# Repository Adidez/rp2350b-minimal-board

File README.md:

# RP2350B Minimal Board — AI-Assisted, Gate-Verified KiCad Project

A Raspberry Pi **RP2350B (QFN-80)** minimal development board, taken from the official reference
design to a **fab-ready, evidence-verified state** by a gated, evidence-first hardware pipeline
with a human decision at every gate.

| | |
|---|---|
| MCU | RP2350B, QFN-80 10×10 mm (order **A4 stepping only** — E9 erratum fixed in A4) |
| Board | 52.6 × 72.1 mm, 2-layer, all 48 GPIOs broken out (8 ADC-capable) |
| Design state | Schematic **ERC: 0 errors** · PCB **DRC: 0 errors**, 73/73 nets connected |
| EDA | KiCad 10.0.4 (design migrated from the official KiCad 7 files, equivalence-proven) |

**Top view** — [checks/pcb_top.png](checks/pcb_top.png) · **Bottom** — [checks/pcb_bottom.png](checks/pcb_bottom.png) · **Schematic PDF** — [checks/schematic_review.pdf](checks/schematic_review.pdf)

## Open the design in KiCad

Two ways:
1. **No git needed**: download [RP2350B_minimal_kicad_project.zip](RP2350B_minimal_kicad_project.zip)
   (or the repo ZIP via *Code ▾ → Download ZIP*), unzip, then double-click
   `design/RP2350_80QFN_minimal.kicad_pro`.
2. `git clone https://github.com/Adidez/rp2350b-minimal-board && open design/RP2350_80QFN_minimal.kicad_pro`

Requires **KiCad 9 or 10** (files are v10 format; project-local symbol + footprint libraries and
the STEP model are included, so it opens fully self-contained — no library setup needed).

## What was actually done (the story)

1. **Stage 0 — Baseline.** Copied the official RP2350B minimal reference (KiCad 7) and migrated
   it under KiCad 10: installed global library tables (117 of 193 findings were phantom config
   noise), added the two missing `PWR_FLAG` declarations on the internal-VREG rails
   (`+1V1`, `VREG_AVDD`) that took ERC from 2 errors → 0, and re-linked a footprint KiCad 10
   renamed. Every schematic edit was proven by **netlist equivalence** — 75/75 nets,
   membership byte-identical.
2. **Stage 1 — Sourcing.** All 39 fitted parts got `MPN` + `LCSC` properties (hidden fields —
   the drawing stays clean) and a per-part datasheet corpus. Live-stock-checked ordering table:
   [checks/G1_gate_report.md](checks/G1_gate_report.md). One engineered substitution
   (Würth button → ALPS SKRPACE010, land-pattern-verified). 9 of 17 lines are JLCPCB Basic tier.
3. **Stage 2/3 — Layout verification.** The official routing was independently re-verified under
   modern checkers: 0 electrical DRC findings, full connectivity (511 segments / 48 vias /
   332 pads), USB pair geometry sound for full-speed, solid bottom GND plane. A false-positive
   severity policy from the KiCad-7 project file was fixed at root cause.
   Evidence: [checks/G3_prevalidation.md](checks/G3_prevalidation.md).
4. **Stage 4 — Fab package: DONE (Gate G4 PASS).** [fab/](fab/) holds the upload-ready set:
   [gerber zip](fab/RP2350B_minimal_gerbers.zip) (7 Protel-ext layers + PTH/NPTH drills,
   drill-count reconciled exactly against the design), [BOM](fab/bom_jlcpcb.csv) (17 lines,
   100% LCSC-resolved), [CPL](fab/cpl_jlcpcb.csv) (39 parts) and
   [ROTATION_NOTES.md](fab/ROTATION_NOTES.md). Release-gate evidence:
   [checks/G4_fab_release_gate.txt](checks/G4_fab_release_gate.txt).

Full audit trail: `git log` — every gate closes with its own commit and report in [checks/](checks/).

## Repository map

```
design/       The working KiCad project (schematic + routed PCB) — ERC/DRC clean
reference/    Official Raspberry Pi minimal design (untouched) + hardware design guide PDF
checks/       Gate reports + ERC/DRC JSON evidence + renders (the generated documents)
datasheets/   Per-MPN vendor datasheets (17) + manifest
fab/          JLCPCB-ready package: gerber zip, assembly BOM (LCSC), CPL, rotation notes
.claude/      The pipeline skill: stage gates, RP2350B design rules, toolchain quirks
```

## The design rules that matter (and that generic AI gets wrong)

- **A4 stepping only** (`RP2350B0A4`, LCSC C9900208890): A2 has erratum E9 (GPIO input-mode
  leakage ~120 µA, latches ~2.2 V). Verify at bring-up via `rp2350_chip_version()`.
- The RP2350 core regulator is a **switcher, not an LDO**: the 3.3 µH inductor
  (Abracon AOTA-B201610S3R3, **polarity dot**) is mandatory.
- `QSPI_SS` is the BOOTSEL strap and `QSPI SD1` selects the bootloader interface — neither may
  be loaded or biased at reset.
- Crystal is CL=10 pF (ABM8-272-T3) with tuned damping — don't substitute a 20 pF part without
  re-deriving load caps.
- Full list with sources: [.claude/skills/rp2350b-hardware-pipeline/references/rp2350b-design-rules.md](.claude/skills/rp2350b-hardware-pipeline/references/rp2350b-design-rules.md)

## Reproduce the verification yourself

```bash
KCLI=/Applications/KiCad/KiCad.app/Contents/MacOS/kicad-cli   # macOS bundle path
$KCLI sch erc --severity-all --output /tmp/erc.rpt design/RP2350_80QFN_minimal.kicad_sch   # → 0 errors
$KCLI pcb drc --severity-all --refill-zones --output /tmp/drc.rpt design/RP2350_80QFN_minimal.kicad_pcb  # → 0 errors
$KCLI pcb render --side top --output /tmp/top.png design/RP2350_80QFN_minimal.kicad_pcb
```

Expected residual warnings are documented (66 `endpoint_off_grid` + 6 `lib_symbol_mismatch` on
the schematic; 52 metadata findings on the PCB) — see the gate reports for the keep-rationale.

## Remaining path to a live board (human steps)

1. **Order at JLCPCB**: upload [fab/RP2350B_minimal_gerbers.zip](fab/RP2350B_minimal_gerbers.zip) +
   [BOM](fab/bom_jlcpcb.csv) + [CPL](fab/cpl_jlcpcb.csv). In the assembly preview, verify
   orientation of U1/U2/U3/J1/L1/Y1 against [checks/pcb_top.png](checks/pcb_top.png) — see
   [fab/ROTATION_NOTES.md](fab/ROTATION_NOTES.md). RP2350B **A4** (C9900208890) is a
   global-sourcing part — reserve early; re-verify all Extended-tier stock (table dated
   2026-07-07). Pick **Standard** assembly if J2/J3 headers should be machine-placed
   (Economic = SMD-only → hand-solder the headers).
2. **Bring-up**: 3V3 → 1V1 (proves VREG + inductor) → hold BOOTSEL, plug USB → mass-storage
   enumeration → flash a UF2 → confirm **A4** in silicon via `rp2350_chip_version()`.

## Attribution & licenses

- Base design: **Raspberry Pi Ltd** — "RP2350B QFN80 Minimal Design Example" from
  [Hardware design with RP2350](https://datasheets.raspberrypi.com/rp2350/hardware-design-with-rp2350.pdf)
  (© Raspberry Pi Ltd, redistributed with attribution; reference copy unmodified in `reference/`).
- Vendor datasheets in `datasheets/` remain the property of their respective manufacturers
  (Winbond, onsemi, Abracon, Samsung, UNI-ROYAL, ALPS, JST, Amphenol, XKB, Raspberry Pi).
- Verification tooling: [KiCad](https://kicad.org) 10.0.4 · [kicad-happy](https://github.com/aklofas/kicad-happy)
  (analysis) · [KiCadRoutingTools](https://github.com/drandyhaas/KiCadRoutingTools) (post-route checks).
- Pipeline definition: project-specific gated skill
  ([.claude/skills/rp2350b-hardware-pipeline](.claude/skills/rp2350b-hardware-pipeline)).

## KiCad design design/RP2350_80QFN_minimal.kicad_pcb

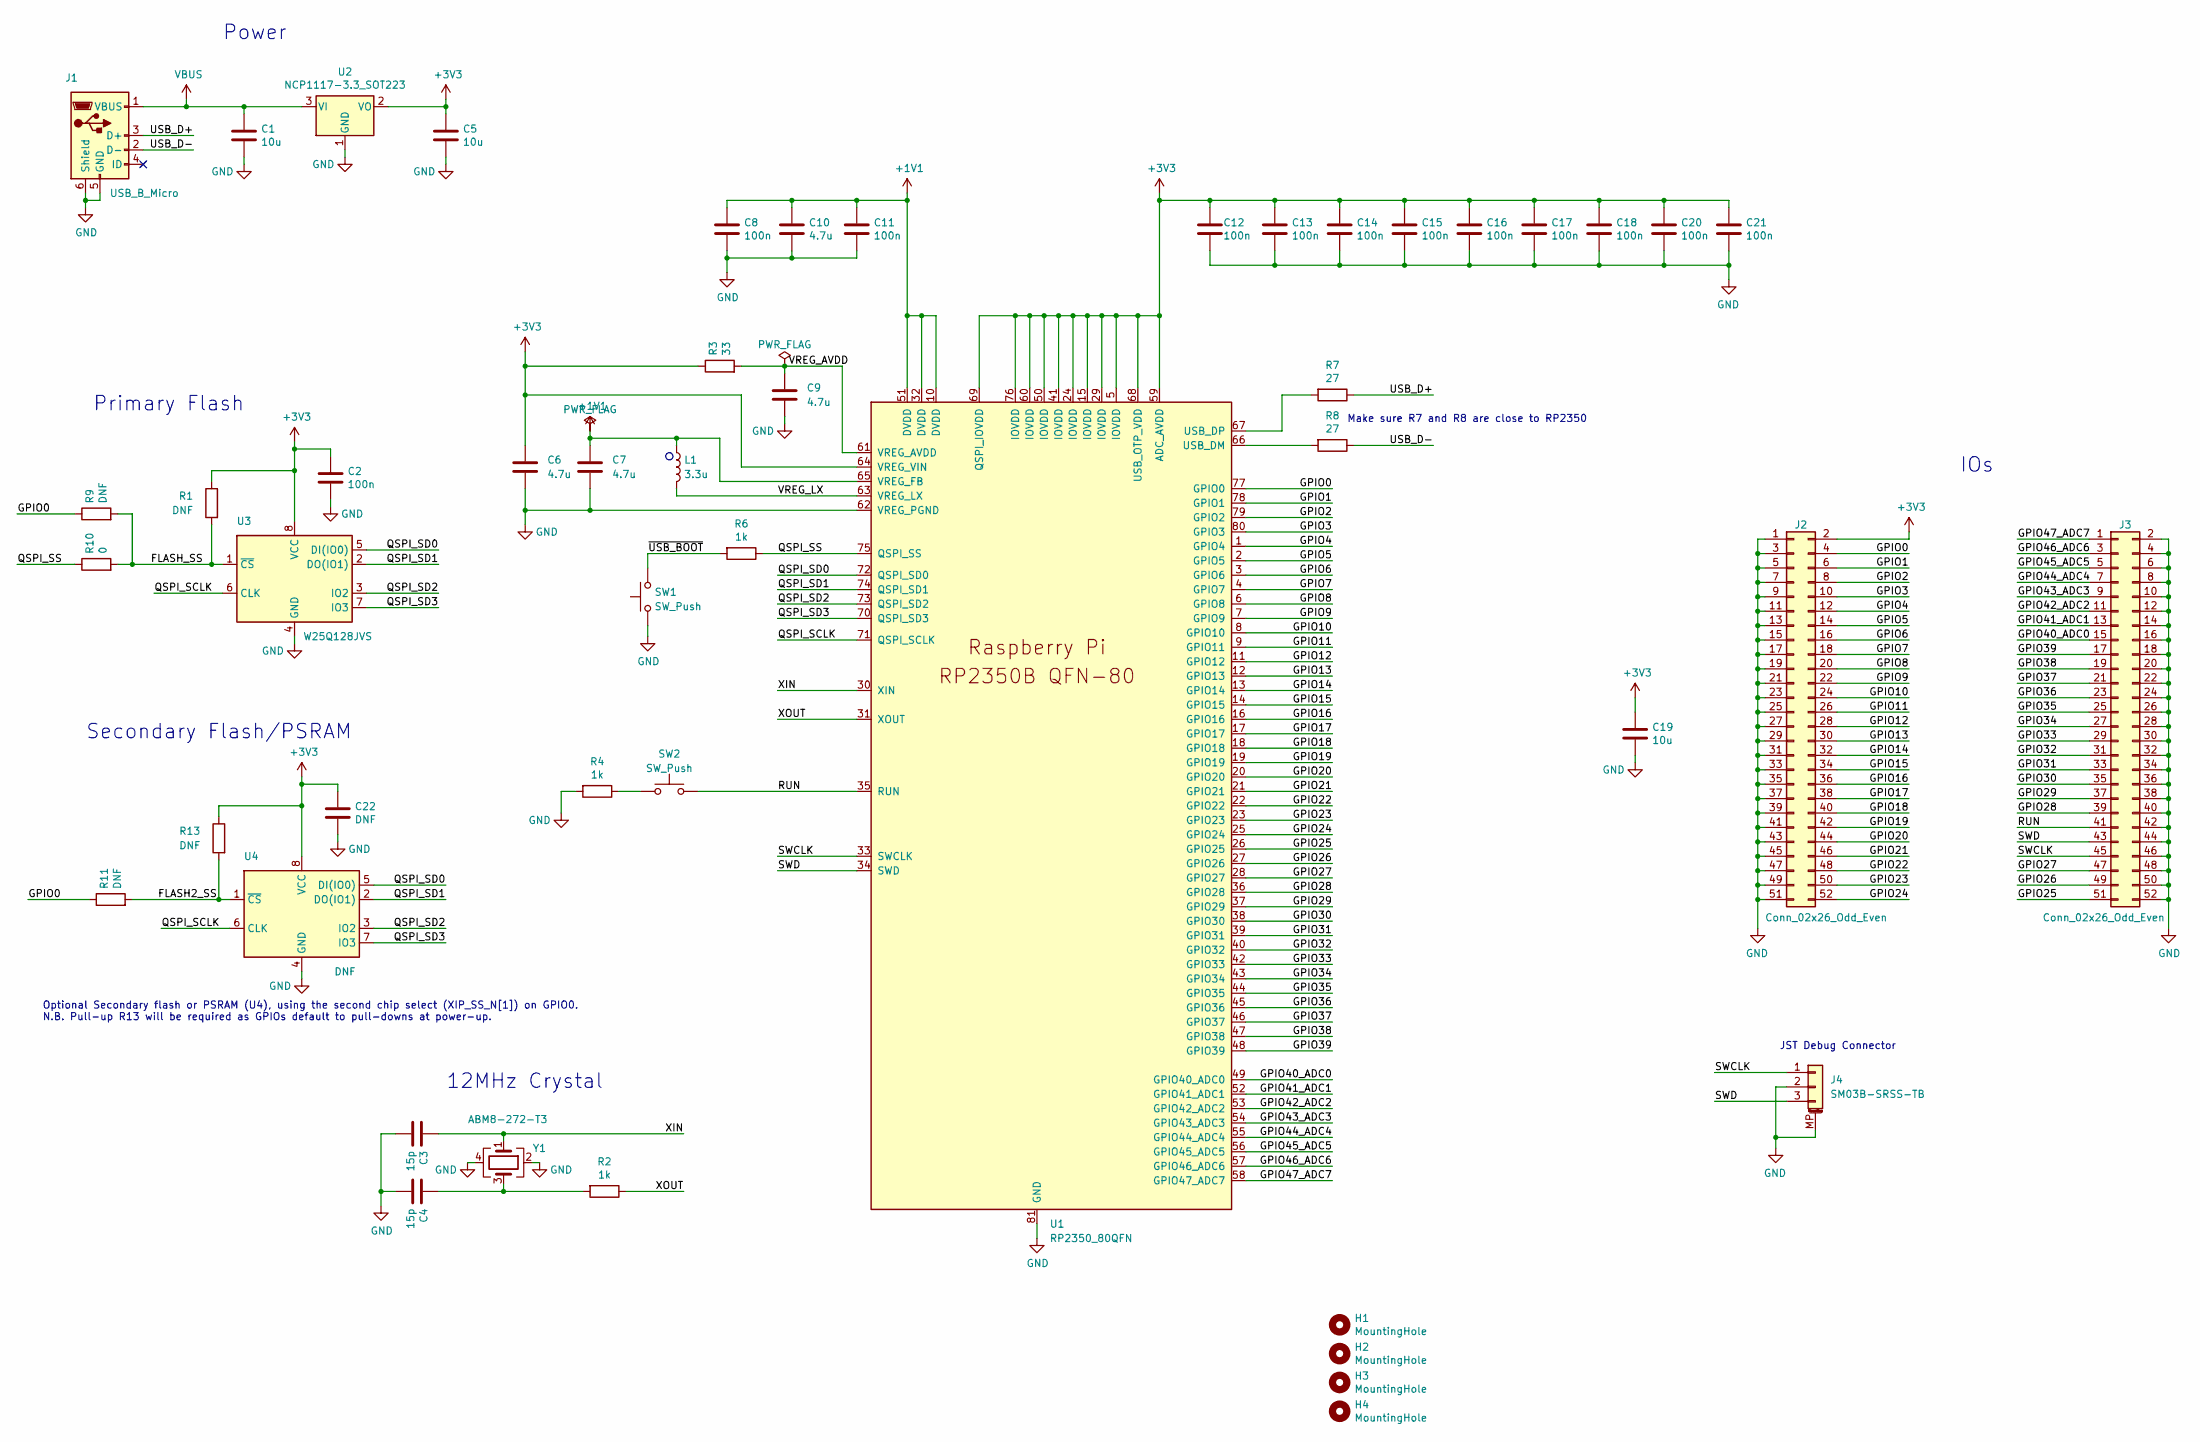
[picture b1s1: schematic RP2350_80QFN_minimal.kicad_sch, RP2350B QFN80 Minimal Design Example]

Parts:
C1, C5, C19: 10u; C_0805_2012Metric; MPN CL21A106KAYNNNE; LCSC C15850
C2, C8, C11, C12, C13, C14, C15, C16, C17, C18, C20, C21: 100n; C_0402_1005Metric; MPN CL05B104KO5NNNC; LCSC C1525
C3, C4: 15p; C_0402_1005Metric; MPN 0402CG150J500NT; LCSC C1548
C6, C7: 4.7u; C_0402_1005Metric_small_pads; MPN CL05A475MP5NRNC; LCSC C23733
C9, C10: 4.7u; C_0402_1005Metric; MPN CL05A475MP5NRNC; LCSC C23733
C22: DNF; C_0402_1005Metric
H1, H2, H3, H4: MountingHole; MountingHole_2.7mm_M2.5
J1: USB_B_Micro; USB_Micro-B_Amphenol_10103594-0001LF_Horizontal; MPN 10103594-0001LF; LCSC C428495
J2, J3: Conn_02x26_Odd_Even; PinHeader_2x26_P2.54mm_Vertical; MPN X6521WV-2x26H-C60D30; LCSC C725898
J4: SM03B-SRSS-TB; JST_SH_SM03B-SRSS-TB_1x03-1MP_P1.00mm_Horizontal; MPN SM03B-SRSS-TB(LF)(SN); LCSC C160403
L1: 3.3u; L_pol_2016; MPN AOTA-B201610S3R3-101-T; LCSC C42411119
R1, R9, R11, R13: DNF; R_0402_1005Metric
R2, R4, R6: 1k; R_0402_1005Metric; MPN 0402WGF1001TCE; LCSC C11702
R3: 33; R_0402_1005Metric; MPN 0402WGF330JTCE; LCSC C25105
R7, R8: 27; R_0402_1005Metric; MPN 0402WGF270JTCE; LCSC C25100
R10: 0; R_0402_1005Metric; MPN 0402WGF0000TCE; LCSC C17168
SW1, SW2: SW_Push; SW_Push_1P1T_NO_Vertical_Wuerth_434133025816; MPN SKRPACE010; LCSC C139797
U1: RP2350_80QFN; RP2350-QFN-80-1EP_10x10_P0.4mm_EP3.4x3.4mm_ThermalVias; MPN RP2350B A4; LCSC C9900208890
U2: NCP1117-3.3_SOT223; SOT-223-3_TabPin2; MPN NCP1117ST33T3G; LCSC C26537
U3: W25Q128JVS; SOIC-8_5.3x5.3mm_P1.27mm; MPN W25Q128JVSIQ; LCSC C97521
U4: DNF; SOIC-8_5.3x5.3mm_P1.27mm
Y1: ABM8-272-T3; Crystal_SMD_3225-4Pin_3.2x2.5mm; MPN ABM8-272-T3; LCSC C20625731

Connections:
+1V1: C7.1, C8.1, C10.1, C11.1, L1.1, U1.10 (DVDD), U1.32 (DVDD), U1.51 (DVDD), U1.65 (VREG_FB)
+3V3: C2.1, C5.1, C6.1, C12.1, C13.1, C14.1, C15.1, C16.1, C17.1, C18.1, C19.1, C20.1, C21.1, C22.1, J2.2, R1.1, R3.1, R13.1, U1.5 (IOVDD), U1.15 (IOVDD), U1.24 (IOVDD), U1.29 (IOVDD), U1.41 (IOVDD), U1.50 (IOVDD), U1.59 (ADC_AVDD), U1.60 (IOVDD), U1.64 (VREG_VIN), U1.68 (USB_OTP_VDD), U1.69 (QSPI_IOVDD), U1.76 (IOVDD), U2.2 (VO), U3.8 (VCC), U4.8 (VCC)
/FLASH2_SS: R11.2, R13.2, U4.1 (~CS)
/FLASH_SS: R1.2, R9.2, R10.2, U3.1 (~CS)
/GPIO0: J2.4, R9.1, R11.1, U1.77 (GPIO0)
/GPIO1: J2.6, U1.78 (GPIO1)
/GPIO2: J2.8, U1.79 (GPIO2)
/GPIO3: J2.10, U1.80 (GPIO3)
/GPIO4: J2.12, U1.1 (GPIO4)
/GPIO5: J2.14, U1.2 (GPIO5)
/GPIO6: J2.16, U1.3 (GPIO6)
/GPIO7: J2.18, U1.4 (GPIO7)
/GPIO8: J2.20, U1.6 (GPIO8)
/GPIO9: J2.22, U1.7 (GPIO9)
/GPIO10: J2.24, U1.8 (GPIO10)
/GPIO11: J2.26, U1.9 (GPIO11)
/GPIO12: J2.28, U1.11 (GPIO12)
/GPIO13: J2.30, U1.12 (GPIO13)
/GPIO14: J2.32, U1.13 (GPIO14)
/GPIO15: J2.34, U1.14 (GPIO15)
/GPIO16: J2.36, U1.16 (GPIO16)
/GPIO17: J2.38, U1.17 (GPIO17)
/GPIO18: J2.40, U1.18 (GPIO18)
/GPIO19: J2.42, U1.19 (GPIO19)
/GPIO20: J2.44, U1.20 (GPIO20)
/GPIO21: J2.46, U1.21 (GPIO21)
/GPIO22: J2.48, U1.22 (GPIO22)
/GPIO23: J2.50, U1.23 (GPIO23)
/GPIO24: J2.52, U1.25 (GPIO24)
/GPIO25: J3.51, U1.26 (GPIO25)
/GPIO26: J3.49, U1.27 (GPIO26)
/GPIO27: J3.47, U1.28 (GPIO27)
/GPIO28: J3.39, U1.36 (GPIO28)
/GPIO29: J3.37, U1.37 (GPIO29)
/GPIO30: J3.35, U1.38 (GPIO30)
/GPIO31: J3.33, U1.39 (GPIO31)
/GPIO32: J3.31, U1.40 (GPIO32)
/GPIO33: J3.29, U1.42 (GPIO33)
/GPIO34: J3.27, U1.43 (GPIO34)
/GPIO35: J3.25, U1.44 (GPIO35)
/GPIO36: J3.23, U1.45 (GPIO36)
/GPIO37: J3.21, U1.46 (GPIO37)
/GPIO38: J3.19, U1.47 (GPIO38)
/GPIO39: J3.17, U1.48 (GPIO39)
/GPIO40_ADC0: J3.15, U1.49 (GPIO40_ADC0)
/GPIO41_ADC1: J3.13, U1.52 (GPIO41_ADC1)
/GPIO42_ADC2: J3.11, U1.53 (GPIO42_ADC2)
/GPIO43_ADC3: J3.9, U1.54 (GPIO43_ADC3)
/GPIO44_ADC4: J3.7, U1.55 (GPIO44_ADC4)
/GPIO45_ADC5: J3.5, U1.56 (GPIO45_ADC5)
/GPIO46_ADC6: J3.3, U1.57 (GPIO46_ADC6)
/GPIO47_ADC7: J3.1, U1.58 (GPIO47_ADC7)
/QSPI_SCLK: U1.71 (QSPI_SCLK), U3.6 (CLK), U4.6 (CLK)
/QSPI_SD0: U1.72 (QSPI_SD0), U3.5 (DI(IO0)), U4.5 (DI(IO0))
/QSPI_SD1: U1.74 (QSPI_SD1), U3.2 (DO(IO1)), U4.2 (DO(IO1))
/QSPI_SD2: U1.73 (QSPI_SD2), U3.3 (IO2), U4.3 (IO2)
/QSPI_SD3: U1.70 (QSPI_SD3), U3.7 (IO3), U4.7 (IO3)
/QSPI_SS: R6.1, R10.1, U1.75 (QSPI_SS)
/RUN: J3.41, SW2.2, U1.35 (RUN)
/SWCLK: J3.45, J4.1, U1.33 (SWCLK)
/SWD: J3.43, J4.3, U1.34 (SWD)
/USB_D+: J1.3 (D+), R7.1
/USB_D-: J1.2 (D-), R8.1
/VREG_AVDD: C9.1, R3.2, U1.61 (VREG_AVDD)
/VREG_LX: L1.2, U1.63 (VREG_LX)
/XIN: C3.1, U1.30 (XIN), Y1.1
/XOUT: R2.1, U1.31 (XOUT)
/~USB_BOOT: R6.2, SW1.2
GND: C1.2, C2.2, C3.2, C4.2, C5.2, C6.2, C7.2, C8.2, C9.2, C10.2, C11.2, C12.2, C13.2, C14.2, C15.2, C16.2, C17.2, C18.2, C19.2, C20.2, C21.2, C22.2, J1.5 (GND), J1.6 (Shield), J2.1, J2.3, J2.5, J2.7, J2.9, J2.11, J2.13, J2.15, J2.17, J2.19, J2.21, J2.23, J2.25, J2.27, J2.29, J2.31, J2.33, J2.35, J2.37, J2.39, J2.41, J2.43, J2.45, J2.47, J2.49, J2.51, J3.2, J3.4, J3.6, J3.8, J3.10, J3.12, J3.14, J3.16, J3.18, J3.20, J3.22, J3.24, J3.26, J3.28, J3.30, J3.32, J3.34, J3.36, J3.38, J3.40, J3.42, J3.44, J3.46, J3.48, J3.50, J3.52, J4.2, J4.MP (MountPin), R4.2, SW1.1, U1.62 (VREG_PGND), U1.81 (GND), U2.1 (GND), U3.4 (GND), U4.4 (GND), Y1.2, Y1.4
unnamed: C4.1, R2.2, Y1.3
unnamed: R4.1, SW2.1
unnamed: R8.2, U1.66 (USB_DM)
unnamed: R7.2, U1.67 (USB_DP)
VBUS: C1.1, J1.1 (VBUS), U2.3 (VI)

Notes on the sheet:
Optional Secondary flash or PSRAM (U4), using the second chip select (XIP_SS_N[1]) on GPIO0. N.B. Pull-up R13 will be required as GPIOs default to pull-downs at power-up.
IOs
12MHz Crystal
Primary Flash
JST Debug Connector
Make sure R7 and R8 are close to RP2350
Secondary Flash/PSRAM
Power

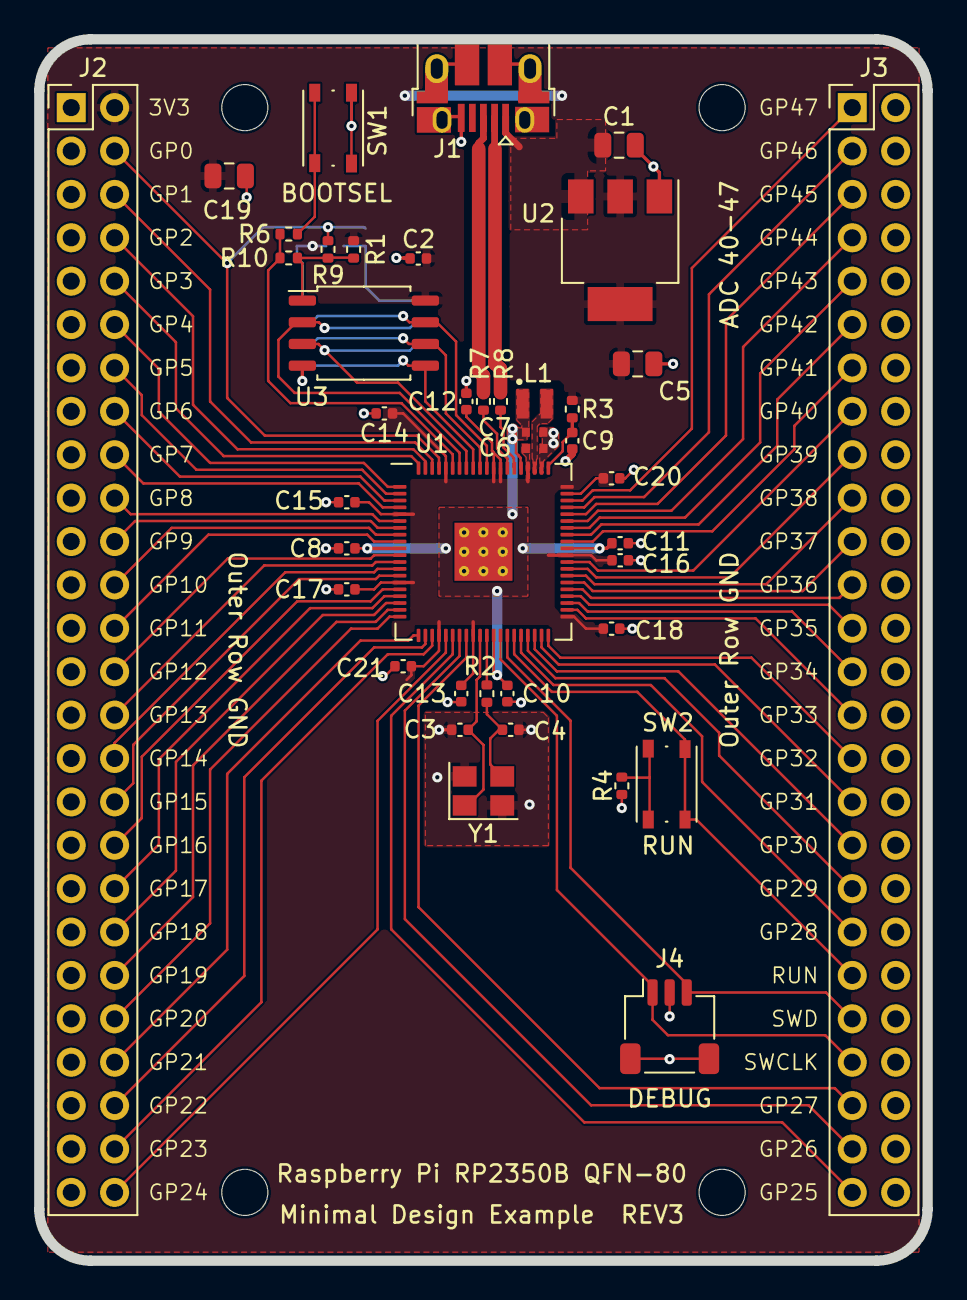
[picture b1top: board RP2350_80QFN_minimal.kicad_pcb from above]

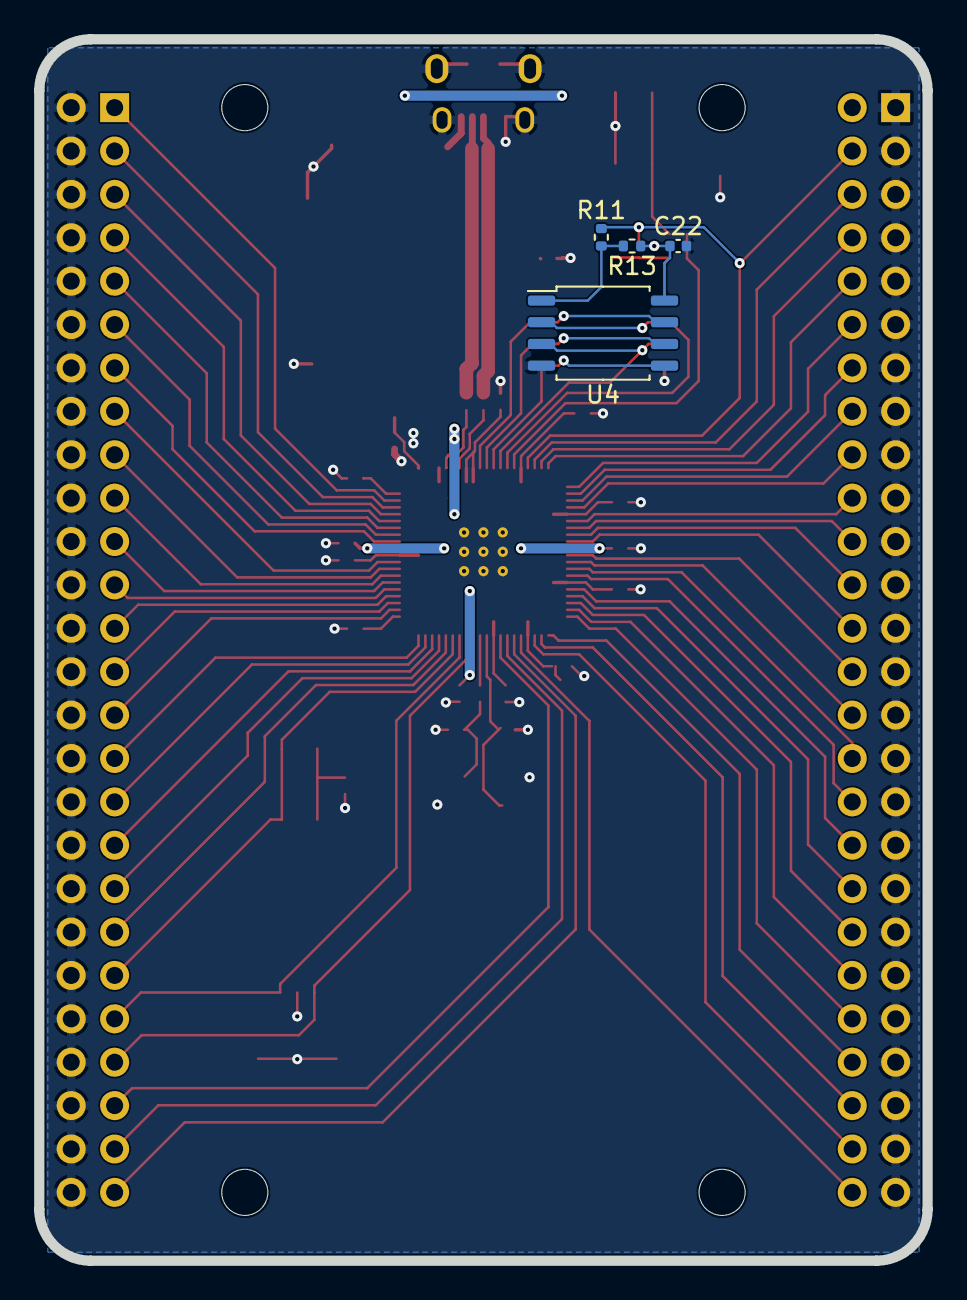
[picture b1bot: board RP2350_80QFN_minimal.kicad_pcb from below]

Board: 2 copper layers, 52.0 x 71.5 mm, 49 parts (4 on the bottom side), 74 nets.

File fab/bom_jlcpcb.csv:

Comment,Designator,Footprint,LCSC Part #
10u,"C1,C5,C19",C_0805_2012Metric,C15850
100n,"C2,C8,C11,C12,C13,C14,C15,C16,C17,C18,C20,C21",C_0402_1005Metric,C1525
15p,"C3,C4",C_0402_1005Metric,C1548
4.7u,"C6,C7,C9,C10",C_0402_1005Metric,C23733
USB_B_Micro,J1,USB_Micro-B_Amphenol_10103594-0001LF_Horizontal,C428495
Conn_02x26_Odd_Even,"J2,J3",PinHeader_2x26_P2.54mm_Vertical,C725898
SM03B-SRSS-TB,J4,JST_SH_SM03B-SRSS-TB_1x03-1MP_P1.00mm_Horizontal,C160403
3.3u,L1,L_pol_2016,C42411119
1k,"R2,R4,R6",R_0402_1005Metric,C11702
33,R3,R_0402_1005Metric,C25105
27,"R7,R8",R_0402_1005Metric,C25100
0,R10,R_0402_1005Metric,C17168
SW_Push,"SW1,SW2",SW_Push_1P1T_NO_Vertical_Wuerth_434133025816,C139797
RP2350_80QFN,U1,RP2350-QFN-80-1EP_10x10_P0.4mm_EP3.4x3.4mm_ThermalVias,C9900208890
NCP1117-3.3_SOT223,U2,SOT-223-3_TabPin2,C26537
W25Q128JVS,U3,SOIC-8_5.3x5.3mm_P1.27mm,C97521
ABM8-272-T3,Y1,Crystal_SMD_3225-4Pin_3.2x2.5mm,C20625731
